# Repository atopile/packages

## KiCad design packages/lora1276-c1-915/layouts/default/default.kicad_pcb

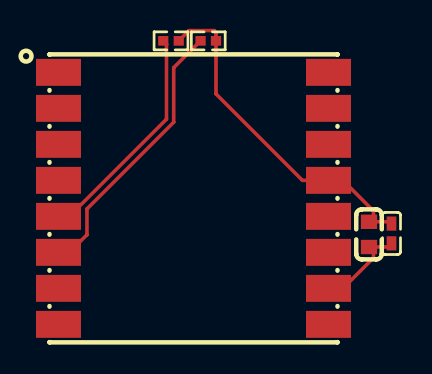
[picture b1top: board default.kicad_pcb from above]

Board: 2 copper layers, 5 parts (0 on the bottom side), 4 nets.

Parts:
C1: 100nF ±10% 16V X7R; C0402
C2: 10µF ±20% 6.3V X5R; C0603
R1, R2: 100kΩ ±1% 62.5mW; R0402
U1: COMM-SMD_LORA1276-C1-915MHZ

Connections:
NRESET: R2.1, U1.6
NSS: R1.1, U1.5
gnd: C1.2, C2.2, U1.1, U1.8, U1.10
hv: C1.1, C2.1, R1.2, R2.2, U1.13

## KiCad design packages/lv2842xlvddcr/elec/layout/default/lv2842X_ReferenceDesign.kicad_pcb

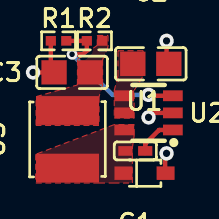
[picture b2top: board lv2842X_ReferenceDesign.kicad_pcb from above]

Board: 2 copper layers, 8 parts (0 on the bottom side), 7 nets.

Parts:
C1: 470nF ±20% 16V X5R; C0402-b3ef17
C2: 4.7µF ±10% 25V X5R; C0805-3b2e55
C3: 10µF ±10% 25V X5R; C0805-3b2e55
R1, R2: 10kΩ ±1% 62.5mW; R0402-56259e
U1: SOD-323_L1.8-W1.3-LS2.5-RD
U2: SOT-23-6_L2.9-W1.6-P0.95-LS2.8-BR
U3: 10µH ±20%; IND-SMD_L4.0-W4.0

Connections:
CB: C1.1, U2.1
FB: R1.1, R2.2, U2.3
SHDN_hash: C2.1, U2.4, U2.5
SW: C1.2, U1.1, U2.6, U3.1
gnd: C2.2, U2.2
gnd-1: C3.2, R1.2, U1.2
hv: C3.1, R2.1, U3.2
